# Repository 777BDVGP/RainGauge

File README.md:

# Rain Gauge

Tipping-bucket rain gauge with an IR beam pickup, outside temperature, rainfall
reports, a daily soil water balance (FAO-56) and an **"irrigate today?"** answer
for an irrigation controller — on a **WEMOS LOLIN S2 Mini** (ESP32-S2). Everything
is a web page on your own WiFi; no cloud, no app needed.

**Install / update page:** https://777bdvgp.github.io/RainGauge/

**How to use it — every page and setting:** [USER_GUIDE.md](USER_GUIDE.md)
(also on the web: https://777bdvgp.github.io/RainGauge/guide.html)

**Contents:** [Features](#features) · [1. Printing the parts](#1-printing-the-parts) ·
[2. Bill of materials](#2-bill-of-materials-bom) · [3. The PCB](#3-the-pcb) ·
[4. The outside temperature sensor](#4-the-outside-temperature-sensor) ·
[5. Assembling the gauge](#5-assembling-the-gauge) ·
[6. Mounting outside](#6-mounting-outside) ·
[7. Installing the firmware](#7-installing-the-firmware) ·
[8. Testing and calibrating](#8-testing-and-calibrating) · [Updating](#updating) ·
[Pin map](#pin-map) · [Building the firmware yourself](#building-the-firmware-yourself) ·
[Licence](#licence)

> **Who this build guide is for:** someone with some hands-on experience — you can
> solder (including a few small SMD parts), use a 3D printer and slicer, and work
> out small details yourself from the photos and STL files. It is not a
> step-by-step kit manual for a complete beginner.
>
> The guide grows while the next gauge is built. Steps marked
> **(to be completed)** get more detail and photos then.

## Features

- **HOME** — live bucket position (IR beam OPEN / BROKEN), rain today / this month,
  last tip, outside temperature, irrigation answer.
- **REPORTS** — three tabs: **RAIN** (rainfall per month / day / hour),
  **TEMPERATURE** (records and daily min / max), **WATER BALANCE** (history).
- **OTHER** — a second row of tabs with SETTINGS, FILES, NTFY and ABOUT:
  - **SETTINGS** — WiFi networks (list, add, delete), funnel size, calibration, tip debounce, IR self-test interval,
    irrigation method (*Water Balance*, *Simple Rule* or *No Irrigation*), controller
    name, START FRESH (clear data, keep settings), SIMULATION.
  - **FILES** — the files on the gauge (view, download, upload, delete).
  - **NTFY** — free push alerts on your phone (ntfy.sh): IR sensor fault, high / low
    outside temperature; IR sensor test with live beam status.
  - **ABOUT** — network, remote access, firmware **update from GitHub** (CHECK / INSTALL).
- **Remote access** — visitors from outside your network (port forward) see only
  HOME and REPORTS; with a password (set on SETTINGS, only from home) they can
  LOG IN for one day and use everything. See the
  [user guide](USER_GUIDE.md#15-remote-access-from-outside-your-home).
- **Self-healing** — restarts when the router stops answering for 1 minute or pages
  are refused for low memory for 30 seconds; after a restart it rejoins the last
  WiFi access point directly, without scanning.
- **`/api/irrigate`** — JSON answer any irrigation controller can poll.

## 1. Printing the parts

All parts were printed in **ABS** on an FDM 3D printer.

**Print them exactly as they are in the STL files — do not rotate them.**
Every part is already saved in its print position: when you load an STL into a
slicer such as **Cura**, it lies on the build plate the right way up, with its
flat side down. Just place it on the plate and slice.

All eight STL files in one download:
[`Enclosure_3D_Print_STL.zip`](https://github.com/777BDVGP/RainGauge/raw/main/Enclosure/Enclosure_3D_Print_STL.zip).
They are also in the [`Enclosure/`](Enclosure) folder — click a name below to
see the part in 3D on GitHub, then **Download raw file** (the download icon at the
top right).

| File | Part | Size (X × Y × height) | ABS approx. |
|---|---|---|---|
| [`RM_Top.stl`](Enclosure/RM_Top.stl) | Top with the funnel — 146 mm across (= *Funnel Diameter* on the SETTINGS page) | 146 × 146 × 88.6 mm | 144 g |
| [`RM_Mid.stl`](Enclosure/RM_Mid.stl) | Middle section | 146 × 146 × 74.5 mm | 135 g |
| [`RM_Base.stl`](Enclosure/RM_Base.stl) | Base | 139 × 115 × 65 mm | 80 g |
| [`RainMeterTipper.stl`](Enclosure/RainMeterTipper.stl) | Tipping bucket | 98 × 23 × 28 mm | 9 g |
| [`PCBLift.stl`](Enclosure/PCBLift.stl) | PCB lift / spacer | 44 × 24 × 3 mm | 2 g |
| [`TempSupportPlug.stl`](Enclosure/TempSupportPlug.stl) | Holder for the outside temperature sensor | 21 × 21 × 17.5 mm | 3 g |
| [`IR_LED_Support.stl`](Enclosure/IR_LED_Support.stl) | Holder for the IR LED (instead of the IR holder PCB) | 24 × 27.6 × 6 mm | 3 g |
| [`Mount_Template.stl`](Enclosure/Mount_Template.stl) | Drilling template for the mounting frame (section 6) | 78.7 × 78.7 × 6 mm | 7 g |

Notes:

- The top and middle need a build plate of at least **150 × 150 mm**.
- Weights are estimates for 3 walls + 20 % infill; all parts together ≈ **390 g** of ABS (with the drilling template).
- ABS warps and cracks when it cools unevenly: an enclosed printer (or a
  draught-free room) and a heated bed help.
- `RainMeterTipper.stl` touches the plate with only a small area — a **brim**
  helps it stay down.
- The tipping bucket must swing freely and the same way to both sides: clean
  any strings or blobs from the pivot after printing.
- After printing, the top and middle are glued, sanded and painted — see
  [section 5](#5-assembling-the-gauge).
- If you change the funnel size, set the new inside diameter on the SETTINGS
  page (*Funnel Diameter*) — the rain in mm is worked out from it.

## 2. Bill of materials (BOM)

Quantities for **one** gauge. Part names in `code` are the names printed on the PCB.

### Main PCB — RAINMETER_V1 (values from [`PCB/RAINMETER_V1.sch`](PCB))

| Qty | Part | On the board | Notes |
|---|---|---|---|
| 1 | PCB RAINMETER_V1 | — | gerbers: [`PCB/RAINMETER_V1_2026-10-04.zip`](PCB) — upload to [PCBWay](https://www.pcbway.com/) (the maker I use and recommend) or any other PCB maker; 2 layers, 1.6 mm, default settings |
| 1 | WEMOS LOLIN S2 Mini (ESP32-S2, 4 MB flash, 2 MB PSRAM) | `ESP32 S2 WEMOS MINI` | |
| 2 + 2 | Pin headers 2 × 8, 2.54 mm | `ESP32 S2 WEMOS MINI` | they come with the S2 Mini when you order it: **male on the PCB**, **female on the S2 Mini** |
| 1 | AMS1117 voltage regulator, SOT-223 | `AMS1` | |
| 1 | 2N2222 transistor, TO-92 | `IR_LED_TR` | switches the IR LED |
| 2 | Resistor 10K, SMD 0805 | `R2`, `R8` | |
| 1 | Resistor 220R, SMD 0805 | `R7` | IR LED current (~16 mA) |
| 2 | Resistor 4K7, SMD 0805 | `R1`, `R3` | DS18S20 pull-ups |
| 3 | Capacitor 220 µF, 25 V electrolytic, 2.5 mm pitch, 5 mm diameter | `C1`, `C2`, `C7` | |
| 1 | Capacitor 0.1 µF ceramic | `C5` | |
| 1 | Screw terminal 2-pin, 5.08 mm pitch | `5VDC_INPUT` | |
| 1 | Molex C-Grid connector 2-pin (70553-02) + mating 2-pin housing and crimps | `IR_LED` | cable to the IR LED |
| 1 | 3-pin header, 2.54 mm | `DS18S20_E` | outside temperature sensor plugs in here |
| 1 | IR pickup: Vishay **BPV11F** — 5 mm NPN phototransistor with daylight filter, for 900–950 nm | `IR PICKUP` | has a **base leg**: not used — only collector and emitter go into the 2 holes (see the note under the BOM) |
| 0–1 | DS18S20, TO-92 | `DS18S20_I` | **optional**, inside temperature (technical use only) |
| 4 | Screws **M3 × 10 mm** for the PCB corners | — | into the brass inserts in the base |

### IR LED — choose one way

| Qty | Part | Notes |
|---|---|---|
| 1 | IR LED: Vishay **TSAL6200** — 5 mm, 940 nm (alternative if out of stock: Everlight IR333-A, also 940 nm) | driven at ~16 mA |
| **either** | | |
| 1 | IR holder PCB RAINMETER_IR_HOLDER + Molex C-Grid 70553-02 connector | gerbers: [`PCB/RAINMETER_IR_HOLDER_2026-11-21.zip`](PCB) |
| **or** | | |
| 1 | Printed holder `IR_LED_Support.stl` | no extra PCB; wires soldered directly onto the LED legs |
| 2 | Wires, 200 mm, different colours | from the IR LED to the `IR_LED` connector |

### Outside temperature sensor

| Qty | Part | Notes |
|---|---|---|
| 1 | DS18S20, TO-92 | |
| 3 | Dupont female crimp terminals | one per leg |
| 1 | Dupont 3-pin housing, 2.54 mm | |
| 1 | Printed holder `TempSupportPlug.stl` | |
| 3 | Wires, 200 mm, different colours | from the sensor to `DS18S20_E` |

### Printed parts and finishing

| Qty | Part | Notes |
|---|---|---|
| 1 each | `RM_Top`, `RM_Mid`, `RM_Base`, `RainMeterTipper`, `PCBLift`, `TempSupportPlug`, `Mount_Template` (+ `IR_LED_Support` if used) | see section 1 |
| ~390 g | ABS filament, 1.75 mm (≈ 155 m) | estimated from the STL files with 3 walls + 20 % infill, without supports; solid (100 % infill) would be ~520 g. One 1 kg spool is plenty |
| — | ABS glue (ABS cement / solvent glue) | top + middle section |
| — | Sandpaper | funnel inside and outside |
| — | White paint (outdoor) | reflects the sun |

### Mechanical

| Qty | Part | Notes |
|---|---|---|
| 20 | Brass heat-set inserts **M3**, **4 mm long** | melted into the base — 16 for the top, 4 for the PCB |
| 16 | Screws **M3 × 25 mm** | top → base, into the brass inserts |
| 1 | Pivot / axle for the tipping bucket, **40 mm** | use a long screw and **cut off the thread at the end**, so the part of the shaft the tipper swings on is **smooth** |
| 1 | Cable gland / grommet for a **10 mm hole** | power and sensor cables in, watertight |
| 1 | **3D printer bed-levelling kit** (M3 bolts, springs and knurled nuts) | for the 4 Ø 3.0 mm mounting holes — the springs let you level the gauge (section 6) |
| — | Mounting hardware (pole, wall bracket, angle iron frame, frame) | **for the builder to improvise** — see section 6; the 4 mounting holes are Ø 3.0 mm on a 68.7 mm square, `Mount_Template.stl` helps to drill the frame |

### Power

| Qty | Part | Notes |
|---|---|---|
| 1 | 5 V DC power supply, at least 1 A — **an old cellphone charger works well** | **check that it gives 5 V DC** (not 9 / 12 V fast-charge, not AC) — measure it before connecting; into `5VDC_INPUT` (**+** marked) |
| 1 | 2-wire power cable, outdoor rated | length to suit where the gauge stands; in through the cable gland |

**About the IR LED and pickup:** the pickup is read with a 10K pull-up — the
input is LOW when it receives light — so it must be an **NPN phototransistor**,
and the LED and pickup must work at the **same wavelength (940 nm)**. A pickup
with a **daylight filter** (black body) is much less disturbed by sunlight. The
recommended pair is the Vishay **TSAL6200** (LED) + **BPV11F** (pickup); any 5 mm
940 nm IR LED + 940 nm NPN phototransistor pair works too.

The BPV11F has a third leg, the **base** — it is not used: look up in its datasheet
which leg is the base, cut it off, and solder **collector and emitter** into the two
`IR PICKUP` holes. If **Bucket Position** on the HOME page never changes when you
tip the bucket, the pickup is the wrong way round — turn it around.

## 3. The PCB

**Ordering the boards:** upload the Gerber ZIP from [`PCB/`](PCB) to [PCBWay](https://www.pcbway.com/) —
I have my own boards made there and can recommend them: easy to order, good quality and quick
delivery. Default settings (2 layers, 1.6 mm) are fine. Any other PCB maker works too.

Solder the parts as printed on the board:

| On the board | Part (from the schematic) |
|---|---|
| `5VDC_INPUT` | 2-pin screw terminal, 5.08 mm pitch — 5 V supply in (**+** marked) |
| `AMS1` | AMS1117 voltage regulator (SOT-223) |
| `ESP32 S2 WEMOS MINI` | pin headers / sockets for the WEMOS LOLIN S2 Mini |
| `IR_LED_TR` | 2N2222 transistor (TO-92) that switches the IR LED |
| `IR_LED` | 2-pin Molex C-Grid connector (70553-02) to the IR LED |
| `IR PICKUP` | 5 mm IR pickup |
| `DS18S20_E` (EXTERNAL) | 3-pin header for the outside DS18S20 |
| `DS18S20_I` (INTERNAL) | optional DS18S20 soldered on the board (inside temperature) |
| `R2`, `R8` | 10K resistors, SMD **0805** |
| `R7` | 220R resistor, SMD 0805 (IR LED current) |
| `R1`, `R3` | 4K7 resistors, SMD 0805 (DS18S20 pull-ups) |
| `C1`, `C2`, `C7` | 220 µF electrolytic capacitors (25 V) |
| `C5` | 0.1 µF ceramic capacitor |

The full schematic is in [`PCB/RAINMETER_V1.sch`](PCB) (Eagle).
Back of the board: [`PCB_BACK.jpg`](docs/pictures/PCB_BACK.jpg).

### The IR LED: two ways to mount it

The IR LED sits opposite the IR pickup, so the tipping bucket breaks the beam
between them. It connects to the `IR_LED` connector on the main PCB.

- **IR holder PCB** — a small extra board, **36.7 × 22.1 mm**, with only the
  5 mm IR LED and a 2-pin connector (Molex C-Grid 70553-02) for the cable to the
  main PCB. Eagle files and gerbers:
  [`PCB/RAINMETER_IR_HOLDER*`](PCB). Neat, but it is one more PCB to order.
- **Printed holder — cheaper alternative:**
  [`IR_LED_Support.stl`](Enclosure/IR_LED_Support.stl) (24 × 27.6 × 6 mm, printed
  like the other parts). No extra PCB needed:
  1. Push the **legs of the IR LED through the two small holes** in the middle of
     the holder.
  2. **Solder the two wires of a cable directly onto the legs** on the other side
     and plug the cable into the `IR_LED` connector on the main PCB
     — mind the **+** (the long leg of the LED is +).
  3. Mount the holder **as shown in the picture below**: on the wall of the base,
     over the hole the beam shines through.

  *The printed holder (grey) on the outside of the wall in the base (blue),
  over the hole the beam shines through.*

## 4. The outside temperature sensor

| | |
|---|---|
|  | **a.** Crimp (or solder) a Dupont female terminal on each leg of the DS18S20. |
|  | **b.** Push the three terminals into a 3-pin housing — keep the leg order. |
|  | **c.** Fit it into `TempSupportPlug`: the sensor sits in the cup... |
|  | **d.** ...and the connector comes out at the bottom. |

It connects to the **EXTERNAL DS18S20_E** header on the PCB. **(to be completed:
where the holder fits on the gauge)**

## 5. Assembling the gauge

**(to be completed)**

**The top and middle section (funnel):**

1. **Glue** the **top** (`RM_Top`) and the **middle section** (`RM_Mid`) together
   with an **ABS glue** (ABS cement / solvent glue for ABS). Let it cure fully.
2. **Sand** the **outside** and the **inside of the funnel** smooth — a smooth funnel
   lets the water run down quickly and leaves no drops behind.
3. **Open the small hole at the bottom of the funnel** properly (drill or file it
   clean): all the water must run through it into the tipping bucket. A half-closed
   hole slows the water down or lets it build up in the funnel.
4. **Paint** it. **White** is best: it reflects the sun, so the gauge (and the
   temperature inside it) heats up as little as possible.

**The base and the electronics:**

5. Melt the 20 **M3 brass inserts** (4 mm long) into the screw holes of the **base**
   (`RM_Base`) with a soldering iron (let them cool before screwing into them).
6. Mount the PCB on the **PCBLift** in the **base** and screw it down with 4 × M3 × 10 mm
   screws into the brass inserts.
7. Fit the **IR LED** (on its holder PCB or in the printed holder) and the
   **IR pickup** into their holes: the holes in the printed parts line them up with
   the **tipping bucket**, so the beam is broken by one side of the bucket and open
   with the other.
8. Put the **tipping bucket** on its pivot (a 40 mm screw with the thread cut off
   where the tipper swings, so the shaft is smooth) — it must tip freely both ways.
9. Connect the IR LED to the `IR_LED` connector, the outside sensor to
   `EXTERNAL DS18S20_E`, and 5 V to `5VDC_INPUT`.

**Putting it together:**

10. Fit the glued **top + middle section** onto the **base** and screw it down with
    16 × M3 × 25 mm screws into the brass inserts.

## 6. Mounting outside

The gauge stands on **4 mounting holes** in the bottom of the base (circled in red):
**Ø 3.0 mm**, on a **68.7 × 68.7 mm square** centred on the gauge (97.2 mm across
the diagonal).

How and where you mount it is up to you — some initiative is needed here. What
works well:

- Make a small frame or plate yourself, e.g. from **angle iron** across a pole,
  a wall bracket or a post, and drill 4 holes in it on the same 68.7 mm square.
- **Drilling template:** print [`Mount_Template.stl`](Enclosure/Mount_Template.stl)
  (a flat plate, 78.7 × 78.7 mm, with the 4 holes in exactly the same places as the
  base). Clamp it on the frame, mark or drill through the holes, and the gauge
  fits.
- Bolt the gauge onto it **with a spring on each bolt** between the base and the
  frame — a **3D printer bed-levelling kit** (M3 bolts, springs, knurled nuts) is
  ideal. With the springs you can **level** the gauge by turning the 4 nuts (like
  the bed of a 3D printer): put a spirit level across the top of the funnel and
  adjust until it is level both ways. A gauge that is not level tips early on one
  side and late on the other, and the readings are wrong.
- Place it in the **open**, away from roofs, walls and trees that shelter it from
  the rain or drip onto it (as a rule of thumb, at least twice the height of the
  obstacle away), with the funnel at a convenient height to clean it.
- Leave room for the power cable and the temperature sensor cable underneath.

## 7. Installing the firmware

No PlatformIO needed:

1. Open the [install page](https://777bdvgp.github.io/RainGauge/) in Chrome or Edge,
   plug the S2 Mini into the PC with a USB **data** cable, press **CONNECT**, choose
   **Erase**, then **Install**. (If no port shows up: hold button **0**, tap **RST**,
   release **0**, try again; tap **RST** once more after the install.)
2. The gauge opens the WiFi hotspot **RainGauge-Setup** (the LED blinks fast).
   Connect a phone to it — the setup page opens by itself (otherwise browse to
   `http://192.168.4.1/`). Pick your network, type the password, choose
   **Automatic (DHCP)** or a **fixed IP**, press **SAVE & RESTART**.
3. Put the phone back on your normal WiFi and open `http://raingauge.local/`
   (or the fixed IP). Use a fixed IP when an irrigation controller must read the gauge.

**More networks:** SETTINGS → **WiFi Networks** lists the saved networks (the
passwords are never shown) with **DELETE**, and **ADD NETWORK** for another one. At
start-up the gauge tries the saved networks in range, strongest first. If none of
them can be reached for about 5 minutes, the **RainGauge-Setup** hotspot opens by
itself for 5 minutes, so you can add a network from a phone (it is added to the
list, not replacing the others).

## 8. Testing and calibrating

1. Set **SETTINGS → Time Zone** (the gauge starts on Greenwich, GMT) and press
   **UPDATE** — before it collects rain, because the reports use local time.
2. Tip the bucket by hand and watch **Bucket Position** on the HOME page:
   it must change between **OPEN** (green) and **BROKEN** (red) on every tip.
3. **NTFY page → TEST IR SENSOR NOW** (with the beam OPEN) must report *OK*.
4. Stand the gauge level and **calibrate** it (SETTINGS → CALIBRATION): pour a known
   amount of water (default 500 ml) slowly into the funnel — the gauge learns how
   much water one tip is.
5. **SETTINGS → START FRESH** to clear the test tips (settings and calibration are kept).
6. Set the **Irrigation Answer Method** (or *No Irrigation* for a plain rain meter),
   your **latitude**, soil type, root depth and garden factor on SETTINGS, and
   NTFY alerts if you want them.

## Updating

ABOUT page → **CHECK FOR UPDATE** → **INSTALL FROM GITHUB**. The new firmware goes
into the spare app slot and is only used when it arrived complete and verified
(HTTPS with certificate check); settings, calibration and rain history are kept.
Without internet at the gauge: install with a USB cable from the install page
(uploading a `.bin` on the ABOUT page was removed in 1.12.1).

## Pin map

| Part | GPIO | Notes |
|---|---|---|
| IR LED (2N2222) | 2 | HIGH = on; LED from 5 V via 220R (~16 mA) |
| IR pickup | 17 | 10k pull-up; LOW = light received, HIGH = beam broken |
| DS18S20 outside | 6 | 4k7 pull-up |
| DS18S20 inside (optional) | 1 | 4k7 pull-up |
| Heartbeat LED | 15 | fast blink = WiFi setup hotspot |

Every change of the pickup (both bucket sides) is one tip.

## Building the firmware yourself

```
cd RainGauge
pio run -e usb -t upload                                  # first time, USB
pio run -e ota -t upload --upload-port <gauge ip>         # later, over WiFi
```

Each build writes `firmware_out/RainGauge_v<ver>.bin` (update) and
`RainGauge_v<ver>_full.bin` (new board). Optional built-in WiFi networks:
`src/wifi_secrets.example.h` (your copy `wifi_secrets.h` is never committed).

Publishing a new version (maintainer): `python sync_from_private.py`, build,
`python update_firmware.py "note"`, commit, push. After changing an STL file:
`python make_enclosure_zip.py` (rebuilds the download ZIP).

## Licence

CC BY-NC 4.0 — see [LICENSE](LICENSE). No warranty: check the irrigation answer
against your own garden before relying on it.

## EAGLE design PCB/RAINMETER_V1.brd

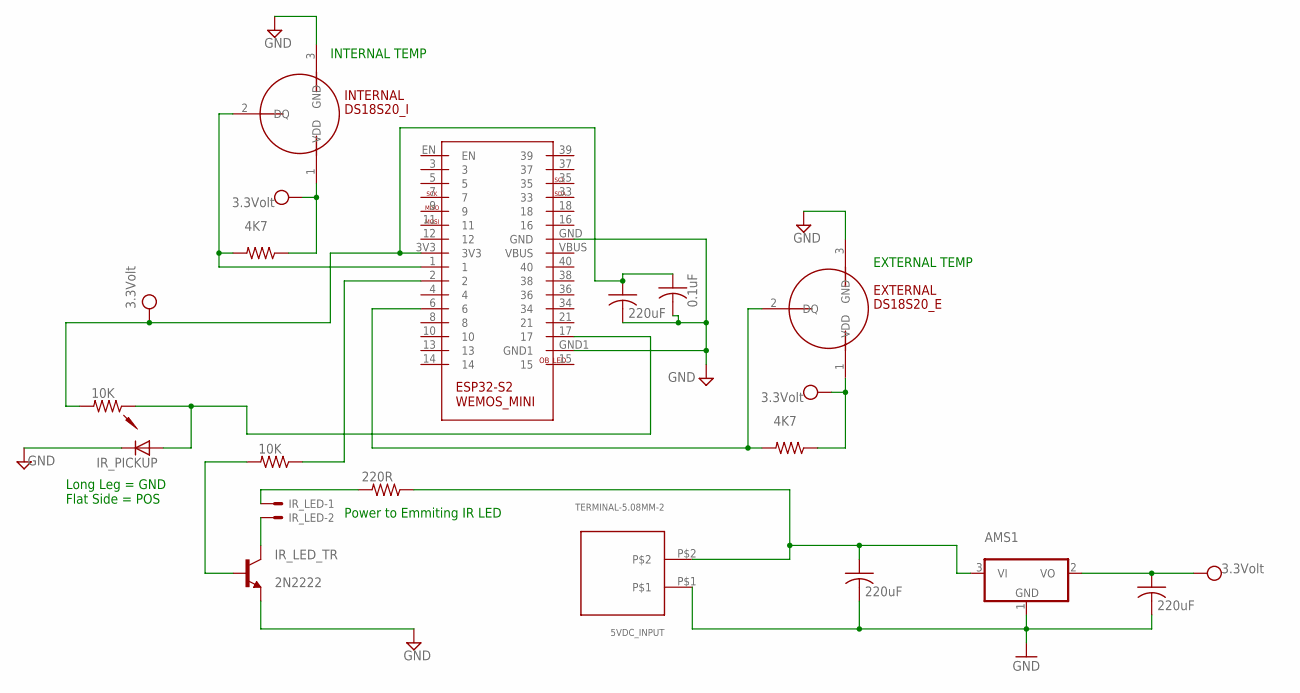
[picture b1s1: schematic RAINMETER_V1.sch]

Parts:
5VDC_INPUT: TERMINAL-5.08MM-2; TERM-5.05-2
AMS1: AMS1117DB; SOT223
C1, C2, C7: 220uF; C3.5-5
C5: 0.1uF; C050-025X075
DS18S20_E: EXTERNAL; TO92-LINE
DS18S20_I: INTERNAL; TO92-LINE
IR_LED: C-GRID-02-70553; 70553-02
IR_LED_TR: 2N2222; TO92-EBC-OVAL
IR_PICKUP: INFRARED_PICKUP5MM; INFRARED_PICKUP
R1, R3: 4K7; R0805
R2, R8: 10K; R0805
R7: 220R; R0805
U$2: WEMOS_S2_MINI

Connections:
GND: 5VDC_INPUT.P$1, AMS1.1 (GND), C1.2, C2.2, C5.2, C7.2, DS18S20_E.3 (GND), DS18S20_I.3 (GND), IR_LED_TR.E, IR_PICKUP.K (C), U$2.GND, U$2.GND1
unnamed: DS18S20_I.2 (DQ), R1.2, U$2.1
unnamed: IR_LED.2, IR_LED_TR.C
unnamed: DS18S20_E.2 (DQ), R3.2, U$2.6
unnamed: IR_LED.1, R7.2
unnamed: IR_LED_TR.B, R2.2
unnamed: R2.1, U$2.2
unnamed: IR_PICKUP.A, R8.1, U$2.17
unnamed: 5VDC_INPUT.P$2, AMS1.3 (VI), C7.1, R7.1
VCC: AMS1.2 (VO), C1.1, C2.1, C5.1, DS18S20_E.1 (VDD), DS18S20_I.1 (VDD), R1.1, R3.1, R8.2, U$2.3V3

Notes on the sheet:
Long Leg = GND Flat Side = POS
Power to Emmiting IR LED
EXTERNAL TEMP
INTERNAL TEMP

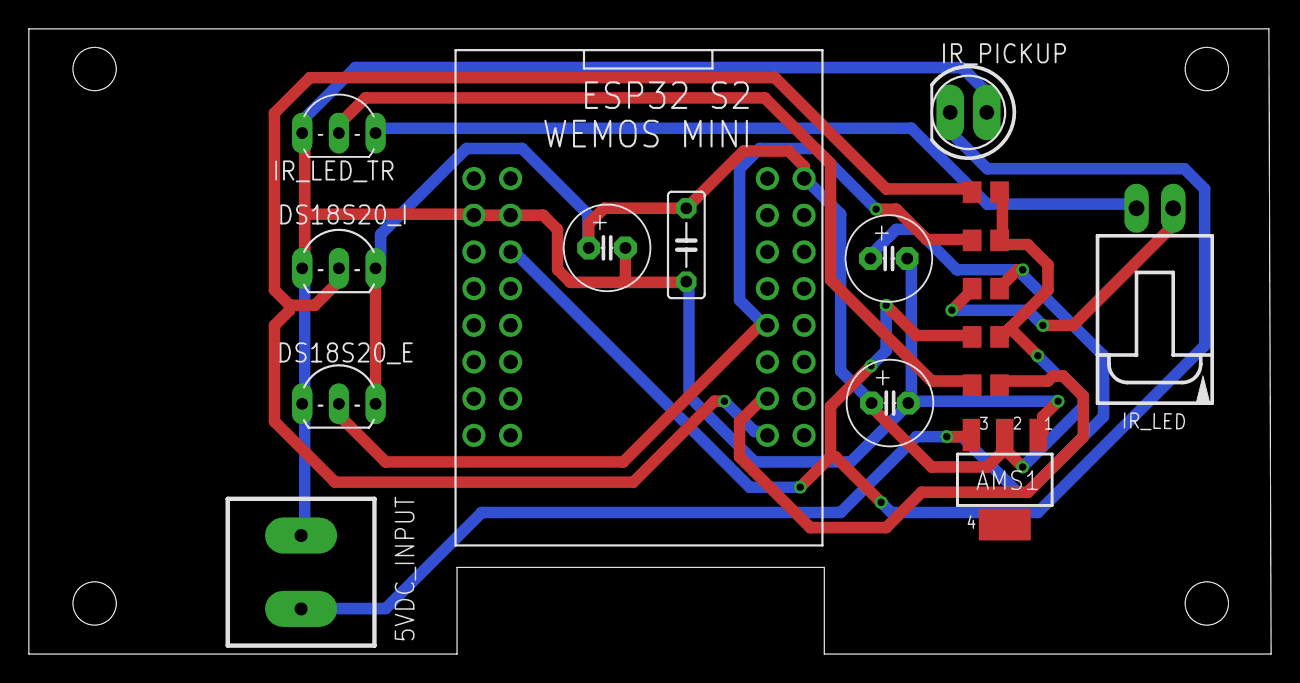
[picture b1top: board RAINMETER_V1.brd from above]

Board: 2 copper layers, 86.0 x 43.3 mm, 17 parts (0 on the bottom side), 10 nets.
